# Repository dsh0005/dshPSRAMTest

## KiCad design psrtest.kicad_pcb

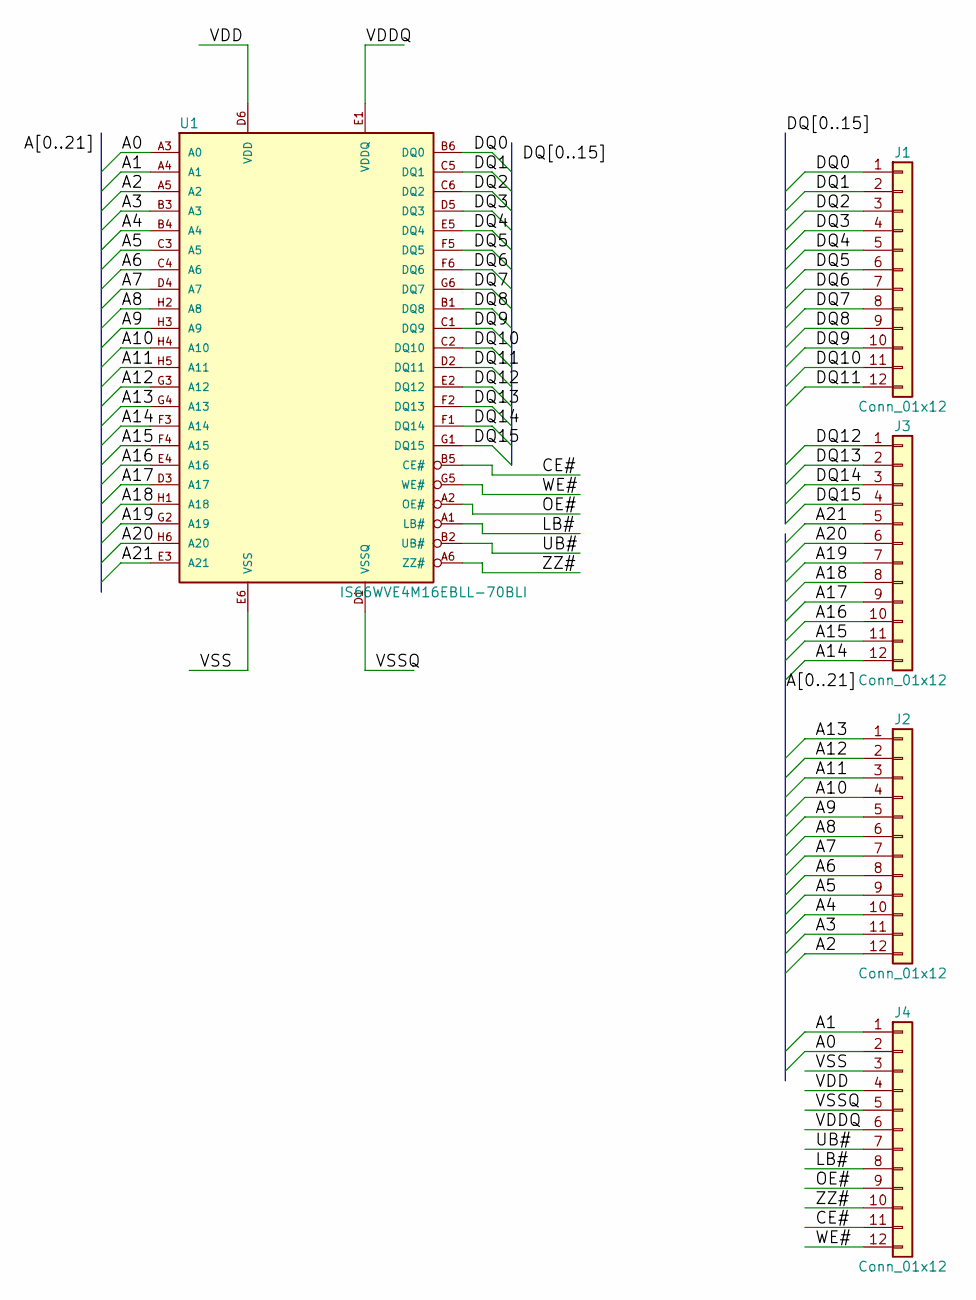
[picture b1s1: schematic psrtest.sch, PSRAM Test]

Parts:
J1, J2, J3, J4: Conn_01x12; Pin_Header_Straight_1x12_Pitch2.54mm
U1: IS66WVE4M16EBLL-70BLI; TFBGA-48

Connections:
/A0: J4.2, U1.A3 (A0)
/A1: J4.1, U1.A4 (A1)
/A2: J2.12, U1.A5 (A2)
/A3: J2.11, U1.B3 (A3)
/A4: J2.10, U1.B4 (A4)
/A5: J2.9, U1.C3 (A5)
/A6: J2.8, U1.C4 (A6)
/A7: J2.7, U1.D4 (A7)
/A8: J2.6, U1.H2 (A8)
/A9: J2.5, U1.H3 (A9)
/A10: J2.4, U1.H4 (A10)
/A11: J2.3, U1.H5 (A11)
/A12: J2.2, U1.G3 (A12)
/A13: J2.1, U1.G4 (A13)
/A14: J3.12, U1.F3 (A14)
/A15: J3.11, U1.F4 (A15)
/A16: J3.10, U1.E4 (A16)
/A17: J3.9, U1.D3 (A17)
/A18: J3.8, U1.H1 (A18)
/A19: J3.7, U1.G2 (A19)
/A20: J3.6, U1.H6 (A20)
/A21: J3.5, U1.E3 (A21)
/CE#: J4.11, U1.B5 (CE#)
/DQ0: J1.1, U1.B6 (DQ0)
/DQ1: J1.2, U1.C5 (DQ1)
/DQ2: J1.3, U1.C6 (DQ2)
/DQ3: J1.4, U1.D5 (DQ3)
/DQ4: J1.5, U1.E5 (DQ4)
/DQ5: J1.6, U1.F5 (DQ5)
/DQ6: J1.7, U1.F6 (DQ6)
/DQ7: J1.8, U1.G6 (DQ7)
/DQ8: J1.9, U1.B1 (DQ8)
/DQ9: J1.10, U1.C1 (DQ9)
/DQ10: J1.11, U1.C2 (DQ10)
/DQ11: J1.12, U1.D2 (DQ11)
/DQ12: J3.1, U1.E2 (DQ12)
/DQ13: J3.2, U1.F2 (DQ13)
/DQ14: J3.3, U1.F1 (DQ14)
/DQ15: J3.4, U1.G1 (DQ15)
/LB#: J4.8, U1.A1 (LB#)
/OE#: J4.9, U1.A2 (OE#)
/UB#: J4.7, U1.B2 (UB#)
/VDD: J4.4, U1.D6 (VDD)
/VDDQ: J4.6, U1.E1 (VDDQ)
/VSS: J4.3, U1.E6 (VSS)
/VSSQ: J4.5, U1.D1 (VSSQ)
/WE#: J4.12, U1.G5 (WE#)
/ZZ#: J4.10, U1.A6 (ZZ#)

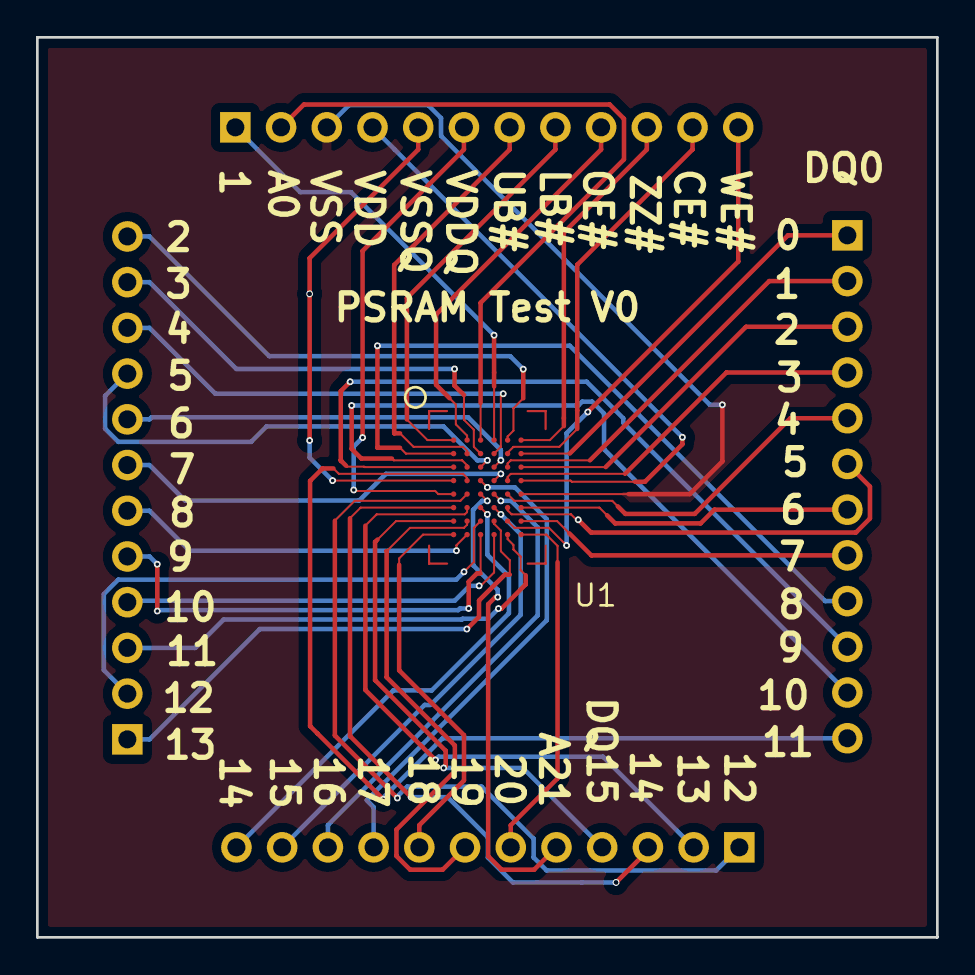
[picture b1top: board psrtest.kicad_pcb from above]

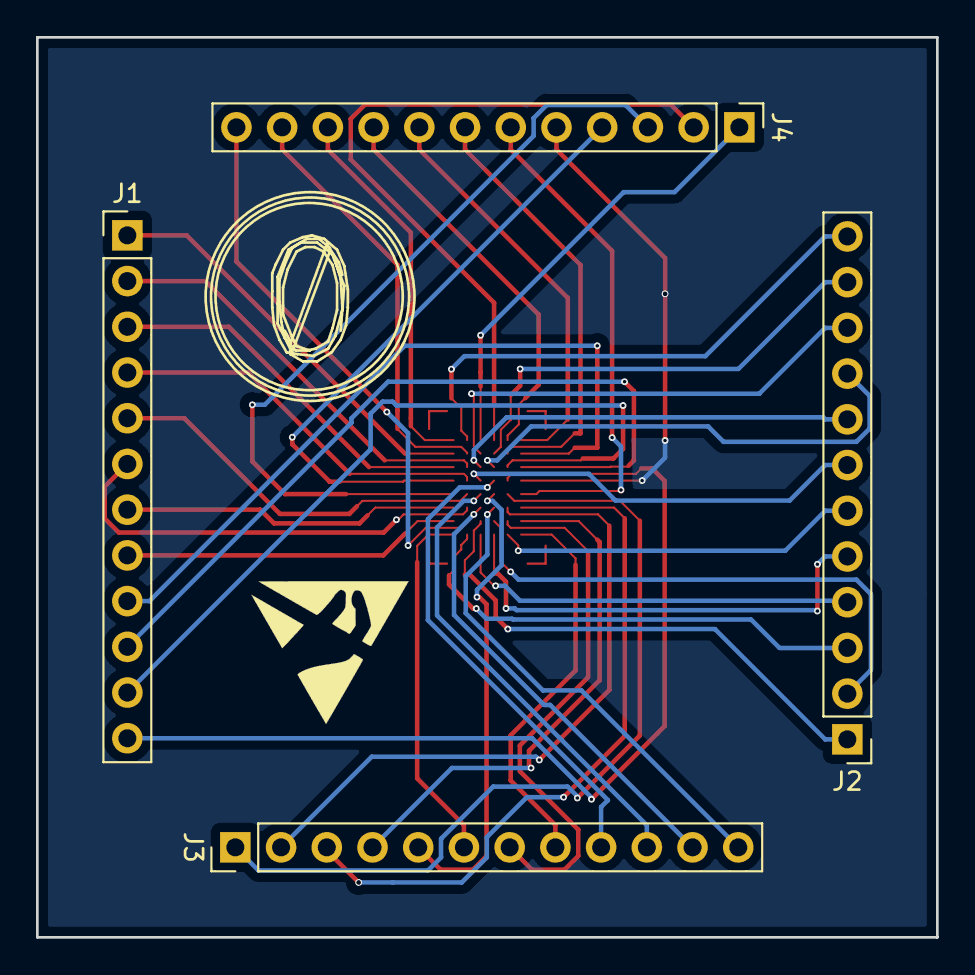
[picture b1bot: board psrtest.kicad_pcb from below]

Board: 2 copper layers, 50.0 x 50.0 mm, 5 parts (4 on the bottom side), 48 nets.

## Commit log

2017-11-27 Add ignore and LICENSE files.
2017-11-27 Add memory IC.
2017-11-29 Initial fanout.
2017-11-29 Autoroute most signals.
2017-11-30 Initial routing cleanup.
2017-11-30 Add some markings.
2017-11-30 Fix a kink in a single trace.
2017-11-30 Actually this is V0. Also mark issue date.
